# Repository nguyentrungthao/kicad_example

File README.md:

# Kiến thức thiết kế sơ đồ nguyên lý

- **Kiến thức cơ bản về điện tử**: [Playlist YouTube](https://www.youtube.com/playlist?list=PLGs3LoDo-2kOWhcLkcdEZovVq_vuPsPHr)
- **Kiến thức về các chuẩn giao tiếp của MCU**: I2C, SPI, UART
- **Kiến thức về nguồn**:
  - **Mạch lọc EMI**: [Video YouTube](https://www.youtube.com/watch?v=QAZo9xbiflQ&t=97s)
  - **Nguồn (Switching Power Supply)**: [Video YouTube](https://www.youtube.com/watch?v=2N_T7VFymFg)
  - **Nguồn xung Buck (Buck Converter)**: [Video YouTube](https://www.youtube.com/watch?v=W6NOV6b8kxs)

---

# KICAD

## Setup phần mềm cài plugin JLC và IBOM

### IBOM:
- [GitHub IBOM Plugin](https://github.com/openscopeproject/InteractiveHtmlBom)
- 

### JLCPCB:
- [GitHub JLCPCB Plugin](https://github.com/Bouni/kicad-jlcpcb-tools)
- **Link điền ở mục 4**: '''https://raw.githubusercontent.com/Bouni/bouni-kicad-repository/main/repository.json'''
- 

---

## Thiết kế phần cứng 
- $${\color{red} NHỚ ĐỌC TÀI LIỆU CỦA LINH KIỆN TRƯỚC KHI VẼ}$$

### Hướng dẫn thêm thư viện IoTVision vào KICAD

#### Thư viện có sẵn 
1. **Vào KICAD**.
2. **Chọn Preferences → Configure Paths**.
3. **Thêm đường dẫn thư viện**:
    - **3D**: Thêm alias như **IOTVISION_3D** và trỏ đường dẫn đến thư mục 3D step.
    - **Symbols**: Thêm alias như **IOTVISION_SYMBOL_DIR** và trỏ đường dẫn đến thư mục symbols.
    - **Footprints**: Thêm alias như **IOTVISION_FOOTPRINT_DIR** và trỏ đường dẫn đến thư mục footprints.
4. Nhấn **OK**.
5. **Quản lý thư viện**:
    - **Preferences → Manage Symbol Libraries → Global Libraries**.
    - Thêm **IVS_SYMBOLS** và đường dẫn thư viện **Symbols.kicad_sym**.
6. **Quản lý Footprint Libraries**:
    - Thêm **IVS_FOOTPRINTS** và đường dẫn **IVSFootprint.pretty**.

> **Lưu ý**: Nếu mở **PCB Editor** hoặc **Footprint Editor**, bạn sẽ không thấy **Manage Symbol Libraries**. 

#### Tải 3D và Footprint

- **Tìm footprint** <tên linh kiện> + <footprint> hoặc <tên linh kiện> + <digikey>
- **Tìm 3D** <tên linh kiện> + <3D> hoặc <Tên linh kiện> + <grabcad>

##### **Tải 3D**:
- [GrabCAD](https://grabcad.com/)
- [3D Content Central](https://www.3dcontentcentral.com/)

##### **Tải Footprint**:
- [SnapEDA](https://www.snapeda.com/)
- [Ultra Librarian](https://www.ultralibrarian.com/)
- [Digi-Key Footprint for Qualcomm RF Front End (RFFE) Filters](https://www.digikey.co.uk/en/products/detail/qualcomm-rf-front-end-rffe-filters/B39871B3725U410/3492646)

- **Video add thư viện**: [Hướng dẫn cài thư viện](https://youtu.be/sz3mICmpLzM)
- **video tìm add thư viện ngoài** [Tải thư viện ngoài - phút 12](https://www.youtube.com/watch?v=1mLzU-ezbA4&list=PLl72apUE_izgVsnWJDfx34R6ak8Qz5oGz&index=2&t=711s)
- **Thư viện cũ của LAB**: [IoTVision](https://github.com/IoTVision/HardwareLibrary)
- **Thư viện riêng của Tác giả** [KicadLIB](https://github.com/nguyentrungthao/KicadLibrary)
---
#### Schematic

1. **Lấy linh kiện**.
2. **Định nghĩa Bus I2C, SPI, Bus số (Demo vẽ insert)**.
3. **Sử dụng Netclass** (định nghĩa class, màu mè cho class).
4. **Thêm hình ảnh** vào Schematic.
5. **Thêm Footprint** cho linh kiện.
6. **Thêm giá trị linh kiện**.
7. **Vẽ Schematic**:
   - Đối với những bạn mới, nên thêm **Solder Jumper** để hạn chế cháy linh kiện.
8. **Thêm mã BOM** cho JLC, Thế Giới IC, IC Đầy Rối.
9. **Xuất BOM**.
10. **Xuất PDF**.

### Các bước khác:
- **Sửa và cập nhật symbol**.
- **Exclude linh kiện khỏi BOM**.
- **Xuất symbol vào thư viện riêng**.

---

#### PCB Design

1. **Thêm thư viện** vào PCB.
2. **Cấu hình board setup**:
   - Thêm/xóa các lớp (4 lớp, 6 lớp).
   - Cấu hình chữ, **Designed Rules**.
   - Cấu hình kích thước track, via, các netclass.
3. **Vẽ viền board** (đúng mm hoặc nhập file DXF).
4. **Vẽ kích thước board**, kích thước vị trí lỗ ốc.
5. **Tạo grid** tùy chỉnh.
6. **Cắt board tạo khoảng trống cách ly**.
7. **Update SCH sang PCB**.
8. **Sửa footprint trực tiếp**.
9. **Layout linh kiện**:
   - Xếp theo chụp các linh kiện, dùng các lệnh sắp xếp linh kiện.
   - Đặt connecter theo vỏ hộp từ đó đặt các linh kiện còn lại.
   - Chia vùng điện áp, vùng phủ đồng và giải thích các lựa chọn phủ đồng: thermal => sold, zone priority.
   - Dùng clearance và giải thích.
   - Rọc lớp đồng để phủ chì.
   - Sắp xếp tinh các linh kiện theo sơ đồ nguyên lý.
   - Đi dây:
     - Đi dây vi sai.
     - Hướng dẫn matching length.
     - Tính trở kháng đường dây.
     - Thêm các via GND.
     - Thêm teardrop.
10. **Xếp chữ ghi, chữ nổi đậm**, edit font chữ nhanh thêm thông tin, logo.
11. **Chạy DRC kiểm lỗi**.
12. **Xuất STEP**.
13. **Xuất PDF**.
14. **Xuất GERBER**.
15. **Xuất CPL**.
16. **Update file lên JLC để review**.

---

### Một số lỗi

- Viền board không nhận => chạy DRC sửa vị trí đỏ.

---
### Danh sách phát video kicad [Kicad play list](https://www.youtube.com/playlist?list=PLl72apUE_izgVsnWJDfx34R6ak8Qz5oGz) 

## HÀN MẠCH

- Học hàn, khò với thiết hàn cuộn và kem chì.
- Học cách tháo connector.

---

## DO NGUỘI

- Đo thông mạch nguồn, các đường tín hiệu trước khi cắm điện.

---

## LẬP TRÌNH TEST MẠCH

- Test nạp code ESP32 => nếu không tự động nạp được, xem lại mạch nút nhấn BOOT và RESET của ESP32.
- Viết code test từng module trên PCB.

## Project Mẫu 
- **STM32F103** [Đồ án môn học - PID Lò nhiệt](https://github.com/nguyentrungthao/AcademicProject2_v2)
- **projet mẫu** [mạch mẫu theo link học tập của Thầy TS.Nguyễn Văn Thái](https://github.com/nguyentrungthao/kicad_example/tree/main/train1)
- **Link bài học của Thầy Nguyễn Văn Thái** [Bài Giảng](https://docs.google.com/document/d/1S12LlzbIVofPXDoD7pqb3iYUZ_utdi-w3tmKryJMrkk/edit?tab=t.0)

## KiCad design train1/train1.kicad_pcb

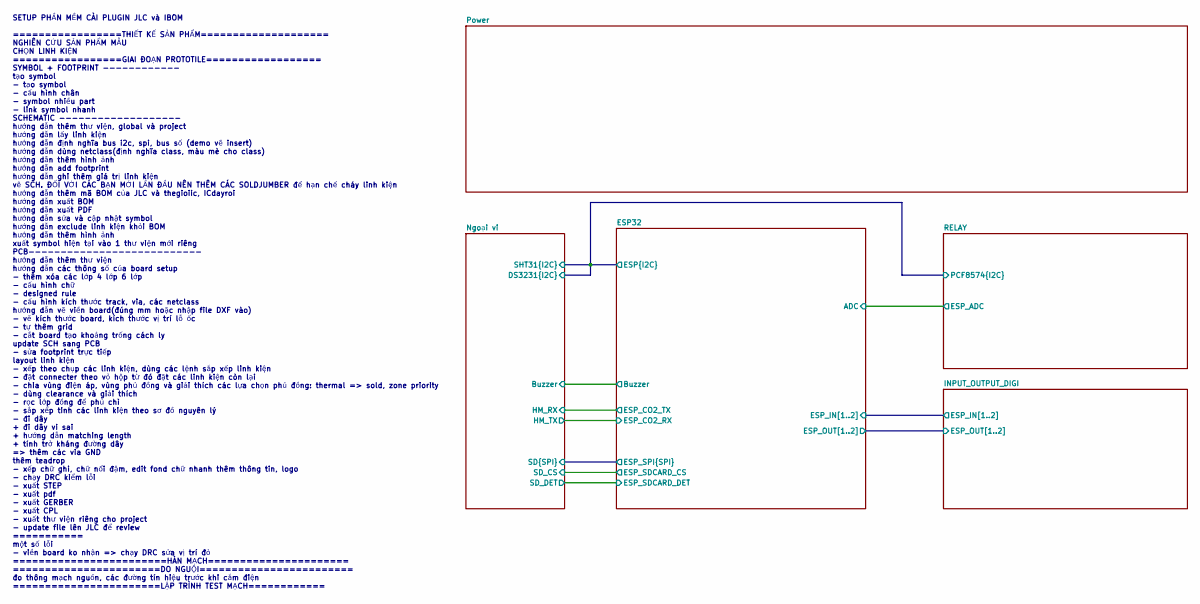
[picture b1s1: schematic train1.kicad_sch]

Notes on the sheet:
SETUP PHẦN MỀM CÀI PLUGIN JLC và IBOM =================THIẾT KẾ SẢN PHẨM==================== NGHIÊN CỨU SẢN PHẨM MẪU CHỌN LINH KIỆN =================GIAI ĐOẠN PROTOTILE================== SYMBOL + FOOTPRINT ------------ tạo symbol - tạo symbol - cấu hình chân - symbol nhiều part - link symbol nhanh 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

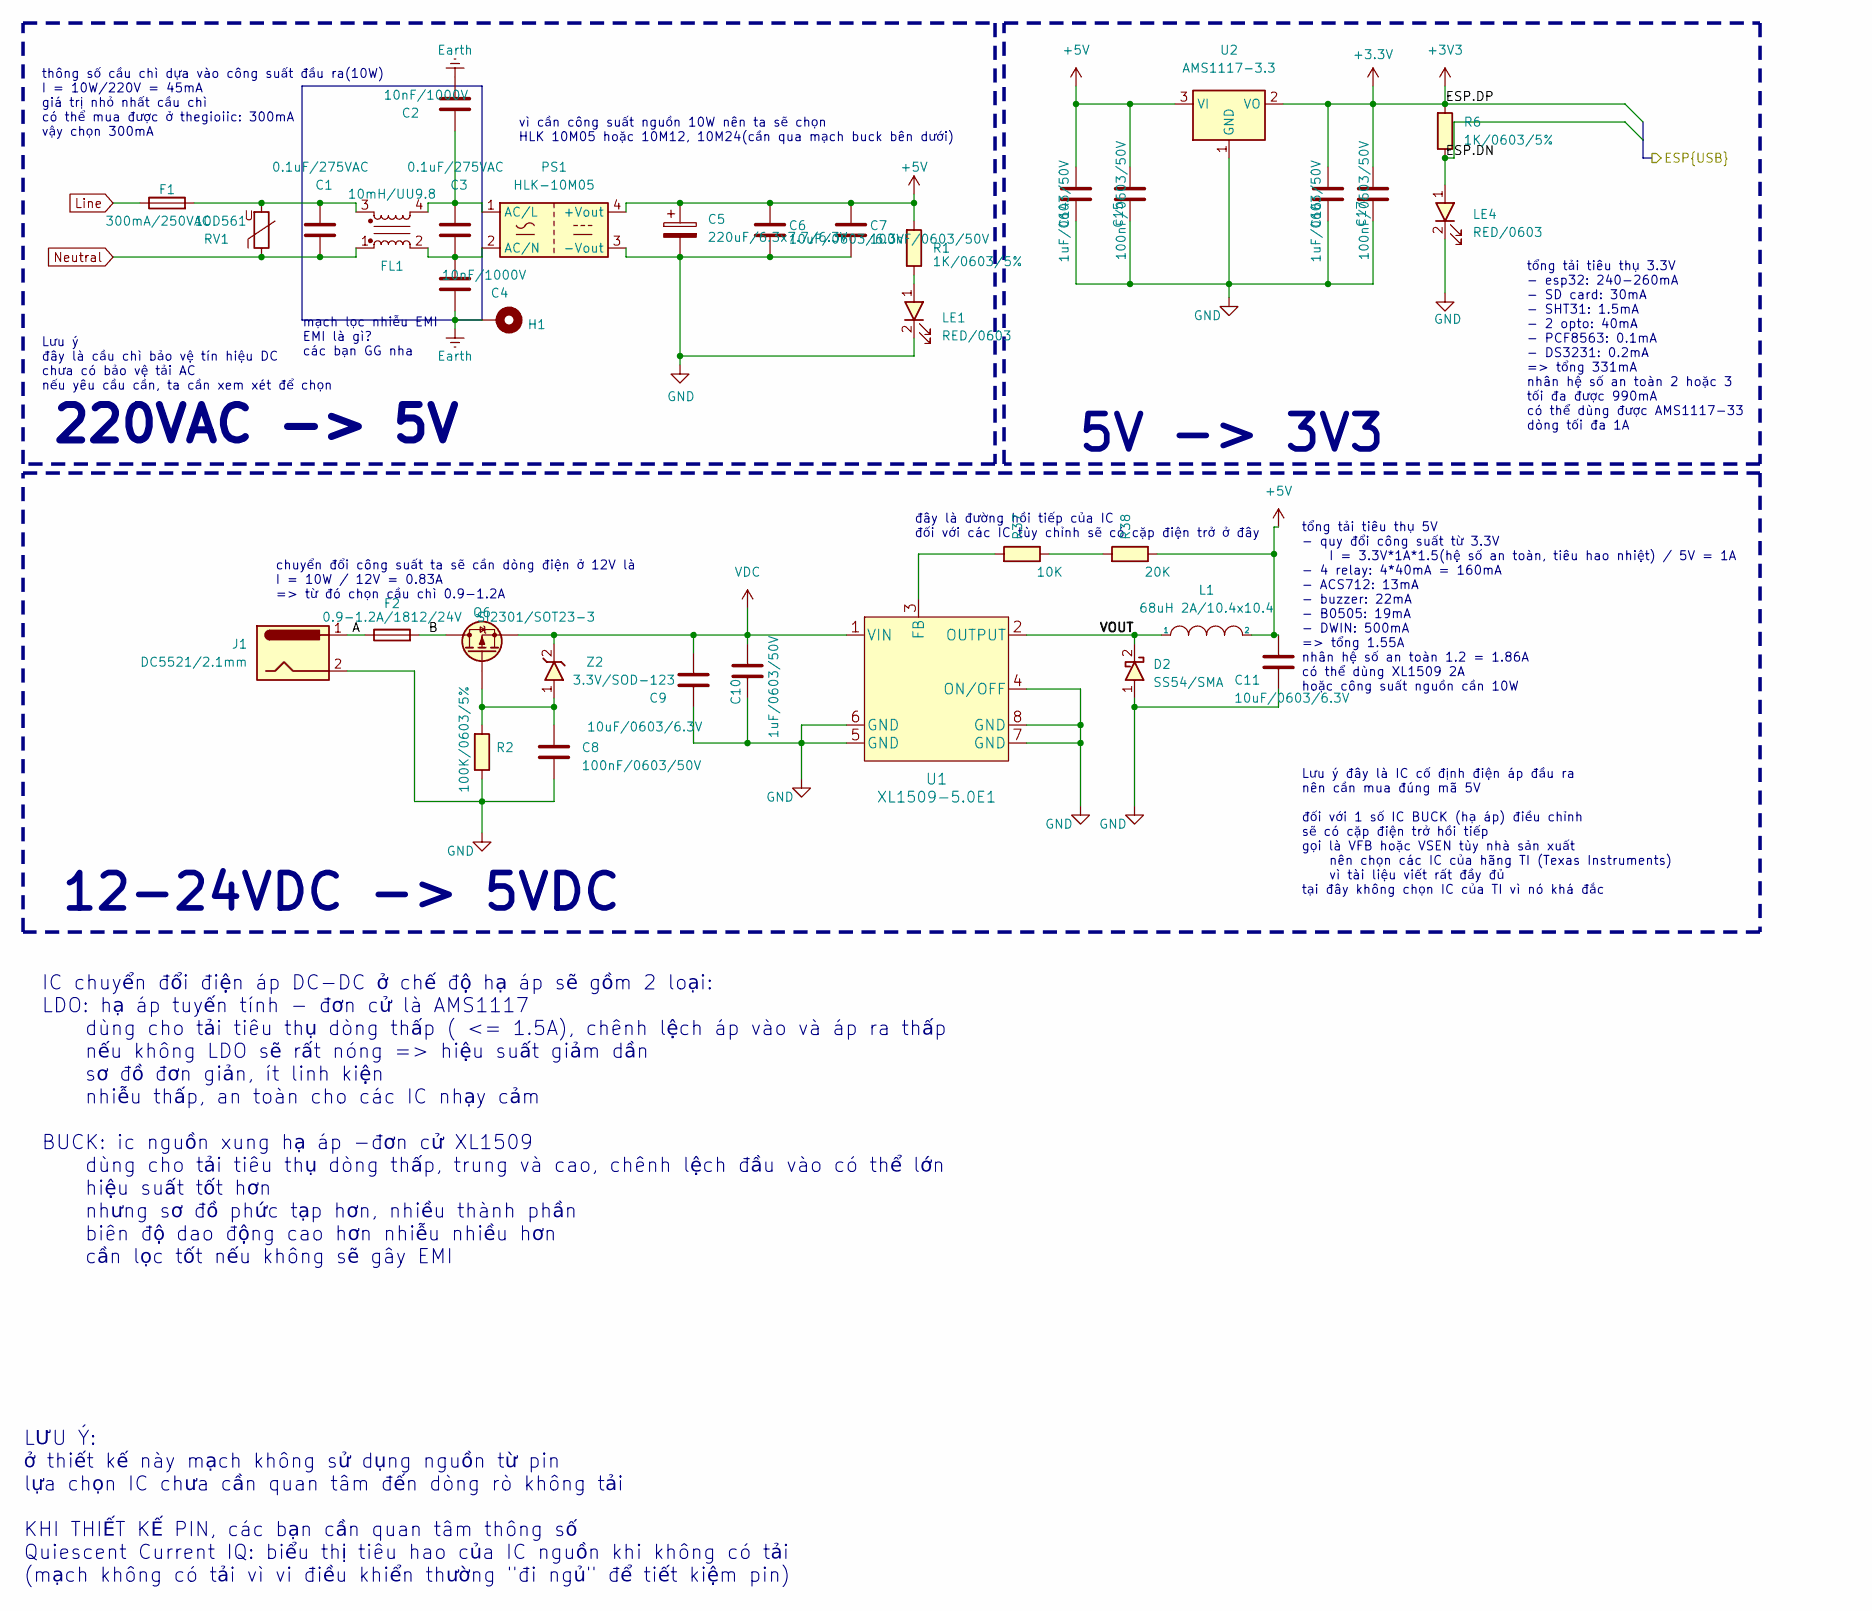
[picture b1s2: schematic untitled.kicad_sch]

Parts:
C1, C3: 0.1uF/275VAC; C_Rect_L16.5mm_W5.0mm_P15.00mm_MKT
C2, C4: 10nF/1000V; C_Rect_L7.0mm_W2.0mm_P5.00mm
C5: 220uF/6.3x7.7/6.3V; CP_Elec_6.3x7.7
C6, C9, C11: 10uF/0603/6.3V; C_0603
C7, C8, C15, C17: 100nF/0603/50V; C_0603
C10, C14, C16: 1uF/0603/50V; C_0603
D2: SS54/SMA; D_SMA
F1: 300mA/250VAC; RV_Disc_D12mm_W3.9mm_P7.5mm
F2: 0.9-1.2A/1812/24V; Fuse_1812_4532Metric
FL1: 10mH/UU9.8; ACFilterChokeUU9.8
H1: MountingHole_Pad; MountingHole_3.2mm_M3_Pad_Via
J1: DC5521/2.1mm; BarrelJack_Wuerth_6941xx301002
L1: 68uH 2A/10.4x10.4; L_10.4x10.4_H4.8
LE1, LE4: RED/0603; LED_0603
PS1: HLK-10M05; ACDC_HLK10M05
Q6: SI2301/SOT23-3; SOT23-3
R1, R6: 1K/0603/5%; C_0603
R2: 100K/0603/5%; C_0603
R37: 10K; C_0603
R38: 20K; C_0603
RV1: 10D561; RV_Disc_D12mm_W5.8mm_P7.5mm
U1: XL1509-5.0E1; SOIC-8_3.9x4.9mm_P1.27mm
U2: AMS1117-3.3; SOT-223-3_TabPin2
Z2: 3.3V/SOD-123; D_SOD-123

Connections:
+3.3V: C16.2, C17.2, R6.1, U2.2 (VO); also elsewhere on the board
+5V: C5.1, C6.1, C7.1, C11.1, C14.2, C15.2, L1.2, PS1.4 (+Vout), R1.1, R38.2, U2.3 (VI); also elsewhere on the board
/Power/A: F2.1, J1.1
/Power/B: F2.2, Q6.3 (D)
/Power/ESP.DN: LE4.1, R6.2
/Power/VOUT: D2.2, L1.1, U1.2 (OUTPUT)
Earth: C2.2, C4.1, H1.1
GND: C5.2, C6.2, C7.2, C8.2, C9.2, C10.1, C11.2, C14.1, C15.1, C16.1, C17.1, D2.1, J1.2, LE1.2, LE4.2, PS1.3 (-Vout), R2.2, U1.4 (ON/OFF), U1.5 (GND), U1.6 (GND), U1.7 (GND), U1.8 (GND), U2.1 (GND); also elsewhere on the board
Line: F1.1; also elsewhere on the board
unnamed: C1.2, F1.2, FL1.3, RV1.2
unnamed: LE1.1, R1.2
unnamed: C2.1, C3.2, FL1.4, PS1.1 (AC/L)
unnamed: C3.1, C4.2, FL1.2, PS1.2 (AC/N)
unnamed: C8.1, Q6.1 (G), R2.1, Z2.1
unnamed: R37.2, R38.1
unnamed: R37.1, U1.3 (FB)
Neutral: C1.1, FL1.1, RV1.1; also elsewhere on the board
VDC: C9.1, C10.2, Q6.2 (S), U1.1 (VIN), Z2.2

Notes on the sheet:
5V -> 3V3
Lưu ý đây là IC cố định điện áp đầu ra nên cần mua đúng mã 5V đối với 1 số IC BUCK (hạ áp) điều chỉnh sẽ có cặp điện trở hồi tiếp gọi là VFB hoặc VSEN tùy nhà sản xuất nên chọn các IC của hãng TI (Texas Instruments) vì tài liệu viết rất đầy đủ tại đây không chọn IC của TI vì nó khá đắc
đây là đường hồi tiếp của IC đối với các IC tùy chỉnh sẽ có cặp điện trở ở đây
LƯU Ý: ở thiết kế này mạch không sử dụng nguồn từ pin lựa chọn IC chưa cần quan tâm đến dòng rò không tải KHI THIẾT KẾ PIN, các bạn cần quan tâm thông số Quiescent Current IQ: biểu thị tiêu hao của IC nguồn khi không có tải (mạch không có tải vì vi điều khiển thường "đi ngủ" để tiết kiệm pin)
chuyển đổi công suất ta sẽ cần dòng điện ở 12V là I = 10W / 12V = 0.83A => từ đó chọn cầu chì 0.9-1.2A
mạch lọc nhiễu EMI EMI là gì? các bạn GG nha
Lưu ý đây là cầu chì bảo vệ tín hiệu DC chưa có bảo vệ tải AC nếu yêu cầu cần, ta cần xem xét để chọn
IC chuyển đổi điện áp DC-DC ở chế độ hạ áp sẽ gồm 2 loại: LDO: hạ áp tuyến tính - đơn cử là AMS1117 dùng cho tải tiêu thụ dòng thấp ( <= 1.5A), chênh lệch áp vào và áp ra thấp nếu không LDO sẽ rất nóng => hiệu suất giảm dần sơ đồ đơn giản, ít linh kiện nhiễu thấp, an toàn cho các IC nhạy cảm BUCK: 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
thông số cầu chì dựa vào công suất đầu ra(10W) I = 10W/220V = 45mA giá trị nhỏ nhất cầu chì có thể mua được ở thegioiic: 300mA vậy chọn 300mA
vì cần công suất nguồn 10W nên ta sẽ chọn HLK 10M05 hoặc 10M12, 10M24(cần qua mạch buck bên dưới)
220VAC -> 5V
12-24VDC -> 5VDC
tổng tải tiêu thụ 3.3V - esp32: 240-260mA - SD card: 30mA - SHT31: 1.5mA - 2 opto: 40mA - PCF8563: 0.1mA - DS3231: 0.2mA => tổng 331mA nhân hệ số an toàn 2 hoặc 3 tối đa được 990mA có thể dùng được AMS1117-33 dòng tối đa 1A
tổng tải tiêu thụ 5V - quy đổi công suất từ 3.3V I = 3.3V*1A*1.5(hệ số an toàn, tiêu hao nhiệt) / 5V = 1A - 4 relay: 4*40mA = 160mA - ACS712: 13mA - buzzer: 22mA - B0505: 19mA - DWIN: 500mA => tổng 1.55A nhân hệ số an toàn 1.2 = 1.86A có thể dùng XL1509 2A hoặc công suất nguồn cần 10W

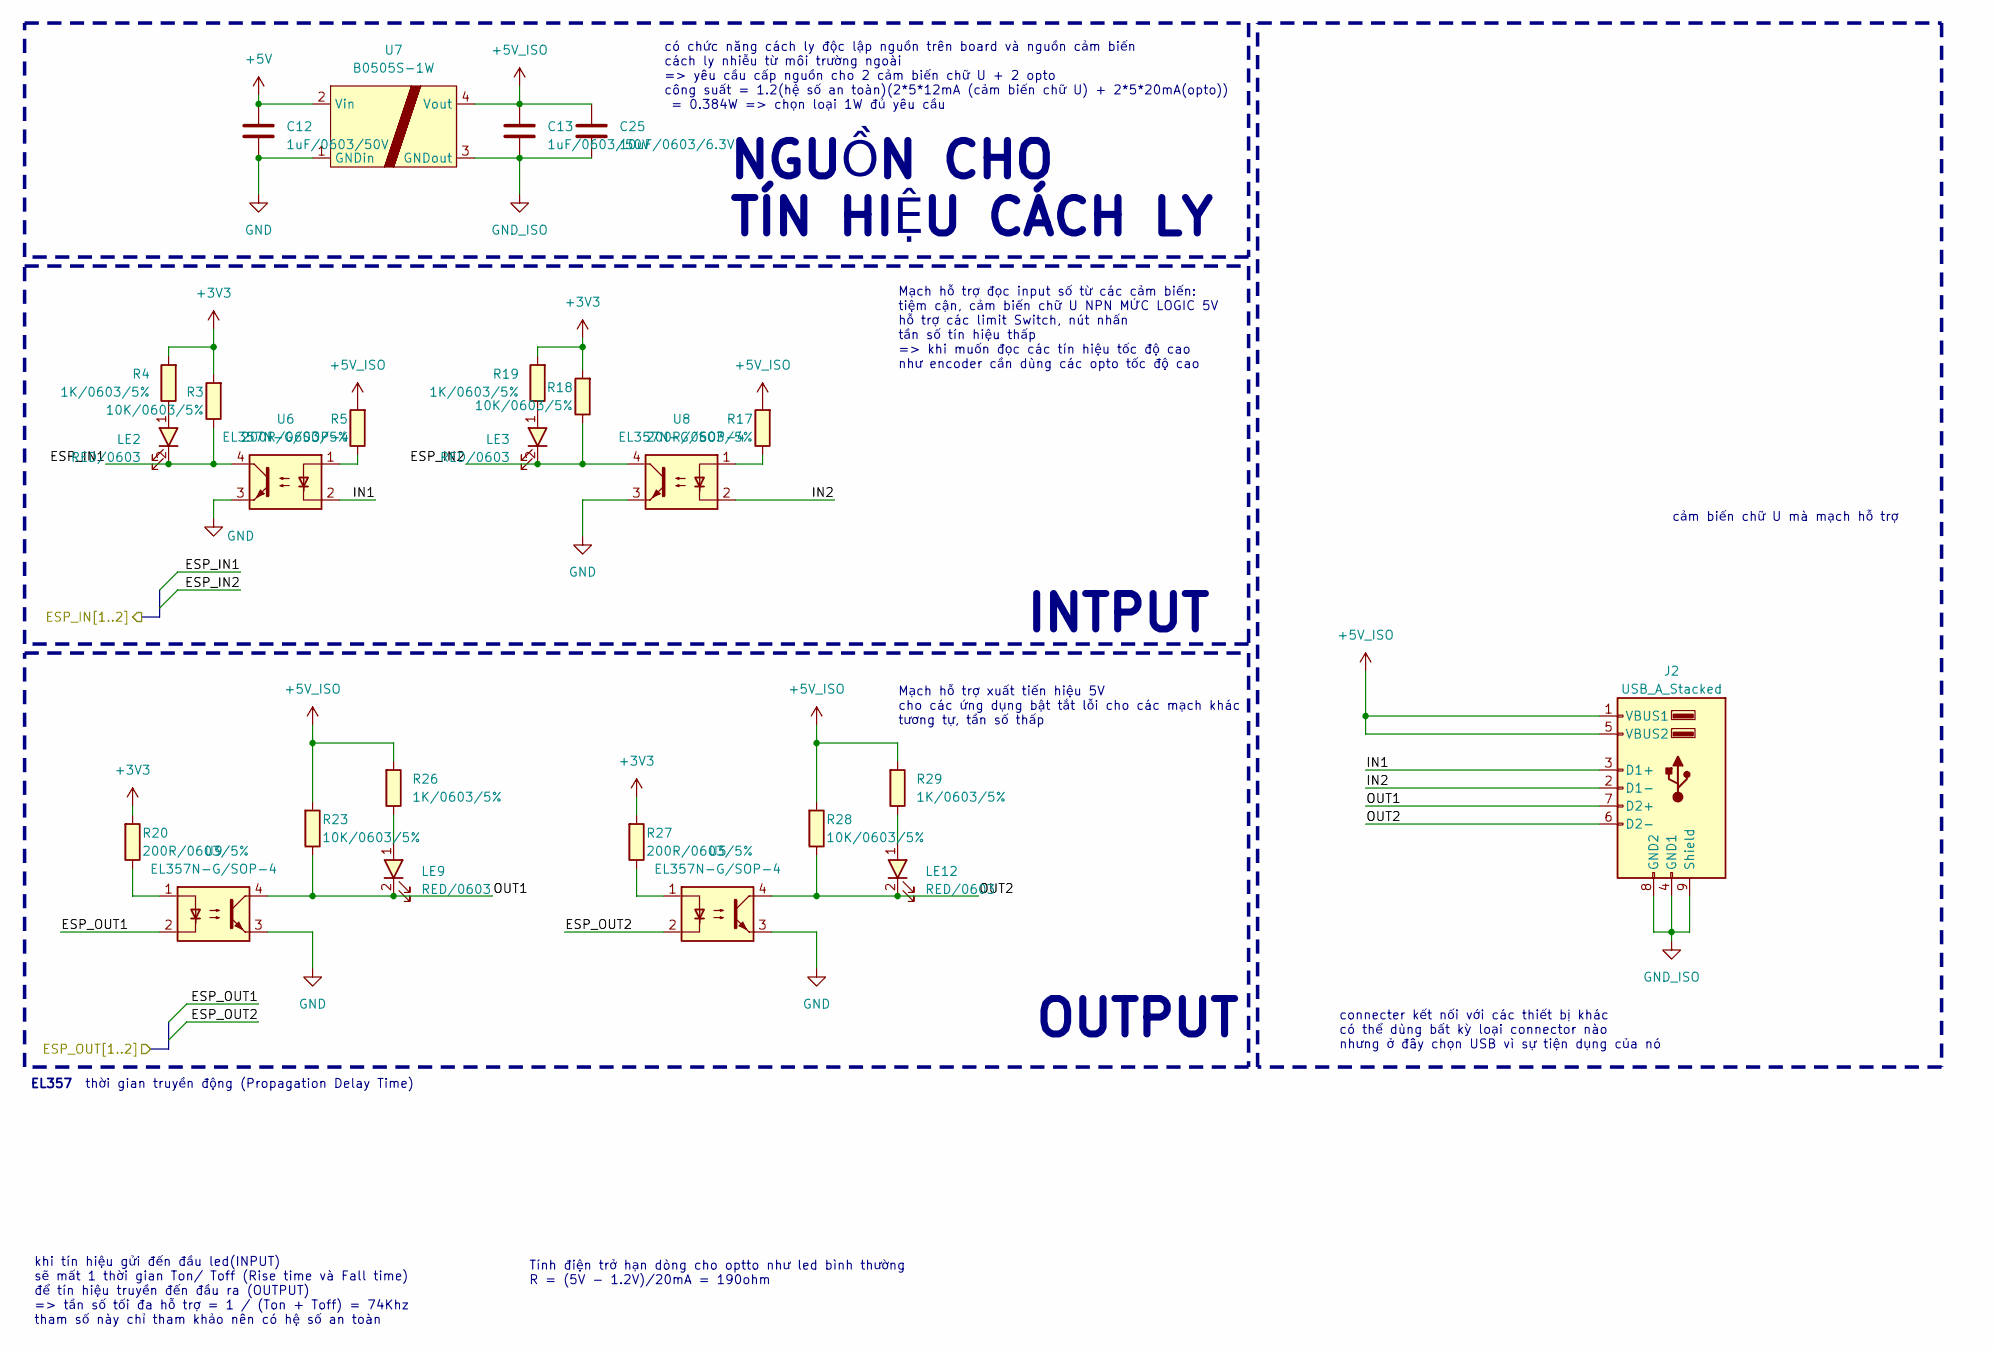
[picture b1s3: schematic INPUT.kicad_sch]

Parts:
C12, C13: 1uF/0603/50V; C_0603
C25: 10uF/0603/6.3V; C_0603
J2: USB_A_Stacked; USB_A_Wuerth_61400826021_Horizontal_Stacked
LE2, LE3, LE9, LE12: RED/0603; LED_0603
R3, R18, R23, R28: 10K/0603/5%; C_0603
R4, R19, R26, R29: 1K/0603/5%; C_0603
R5, R17, R20, R27: 200R/0603/5%; C_0603
U5, U6, U8, U9: EL357N-G/SOP-4; OPTO_EL357N-G
U7: B0505S-1W; B0505S

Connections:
+3.3V: R3.1, R4.1, R18.1, R19.1, R20.1, R27.1; also elsewhere on the board
+5V: C12.1, U7.2 (Vin); also elsewhere on the board
+5V_ISO: C13.1, C25.1, J2.1 (VBUS1), J2.5 (VBUS2), R5.1, R17.1, R23.1, R26.1, R28.1, R29.1, U7.4 (Vout)
/ESP32/ESP_IN1: LE2.2, R3.2, U6.4; also elsewhere on the board
/ESP32/ESP_IN2: LE3.2, R18.2, U8.4; also elsewhere on the board
/ESP32/ESP_OUT1: U9.2; also elsewhere on the board
/ESP32/ESP_OUT2: U5.2; also elsewhere on the board
/INPUT_OUTPUT_DIGI/IN1: J2.3 (D1+), U6.2
/INPUT_OUTPUT_DIGI/IN2: J2.2 (D1-), U8.2
/INPUT_OUTPUT_DIGI/OUT1: J2.7 (D2+), LE9.2, R23.2, U9.4
/INPUT_OUTPUT_DIGI/OUT2: J2.6 (D2-), LE12.2, R28.2, U5.4
GND: C12.2, U5.3, U6.3, U7.1 (GNDin), U8.3, U9.3; also elsewhere on the board
GND_ISO: C13.2, C25.2, J2.4 (GND1), J2.8 (GND2), J2.9 (Shield), U7.3 (GNDout)
unnamed: LE2.1, R4.2
unnamed: LE3.1, R19.2
unnamed: LE9.1, R26.2
unnamed: LE12.1, R29.2
unnamed: R5.2, U6.1
unnamed: R17.2, U8.1
unnamed: R20.2, U9.1
unnamed: R27.2, U5.1

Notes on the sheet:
cảm biến chữ U mà mạch hỗ trợ
OUTPUT
khi tín hiệu gửi đến đầu led(INPUT) sẽ mất 1 thời gian Ton/ Toff (Rise time và Fall time) để tín hiệu truyền đến đầu ra (OUTPUT) => tần số tối đa hỗ trợ = 1 / (Ton + Toff) = 74Khz tham số này chỉ tham khảo nên có hệ số an toàn
connecter kết nối với các thiết bị khác có thể dùng bất kỳ loại connector nào nhưng ở đây chọn USB vì sự tiện dụng của nó
Tính điện trở hạn dòng cho optto như led bình thường R = (5V - 1.2V)/20mA = 190ohm
Mạch hỗ trợ đọc input số từ các cảm biến: tiệm cận, cảm biến chữ U NPN MỨC LOGIC 5V hỗ trợ các limit Switch, nút nhấn tần số tín hiệu thấp => khi muốn đọc các tín hiệu tốc độ cao như encoder cần dùng các opto tốc độ cao
thời gian truyền động (Propagation Delay Time)
EL357
NGUỒN CHO TÍN HIỆU CÁCH LY
có chức năng cách ly độc lập nguồn trên board và nguồn cảm biến cách ly nhiễu từ môi trường ngoài => yêu cầu cấp nguồn cho 2 cảm biến chữ U + 2 opto công suất = 1.2(hệ số an toàn)(2*5*12mA (cảm biến chữ U) + 2*5*20mA(opto)) = 0.384W => chọn loại 1W đủ yêu cầu
INTPUT
Mạch hỗ trợ xuất tiến hiệu 5V cho các ứng dụng bật tắt lỗi cho các mạch khác tương tự, tần số thấp

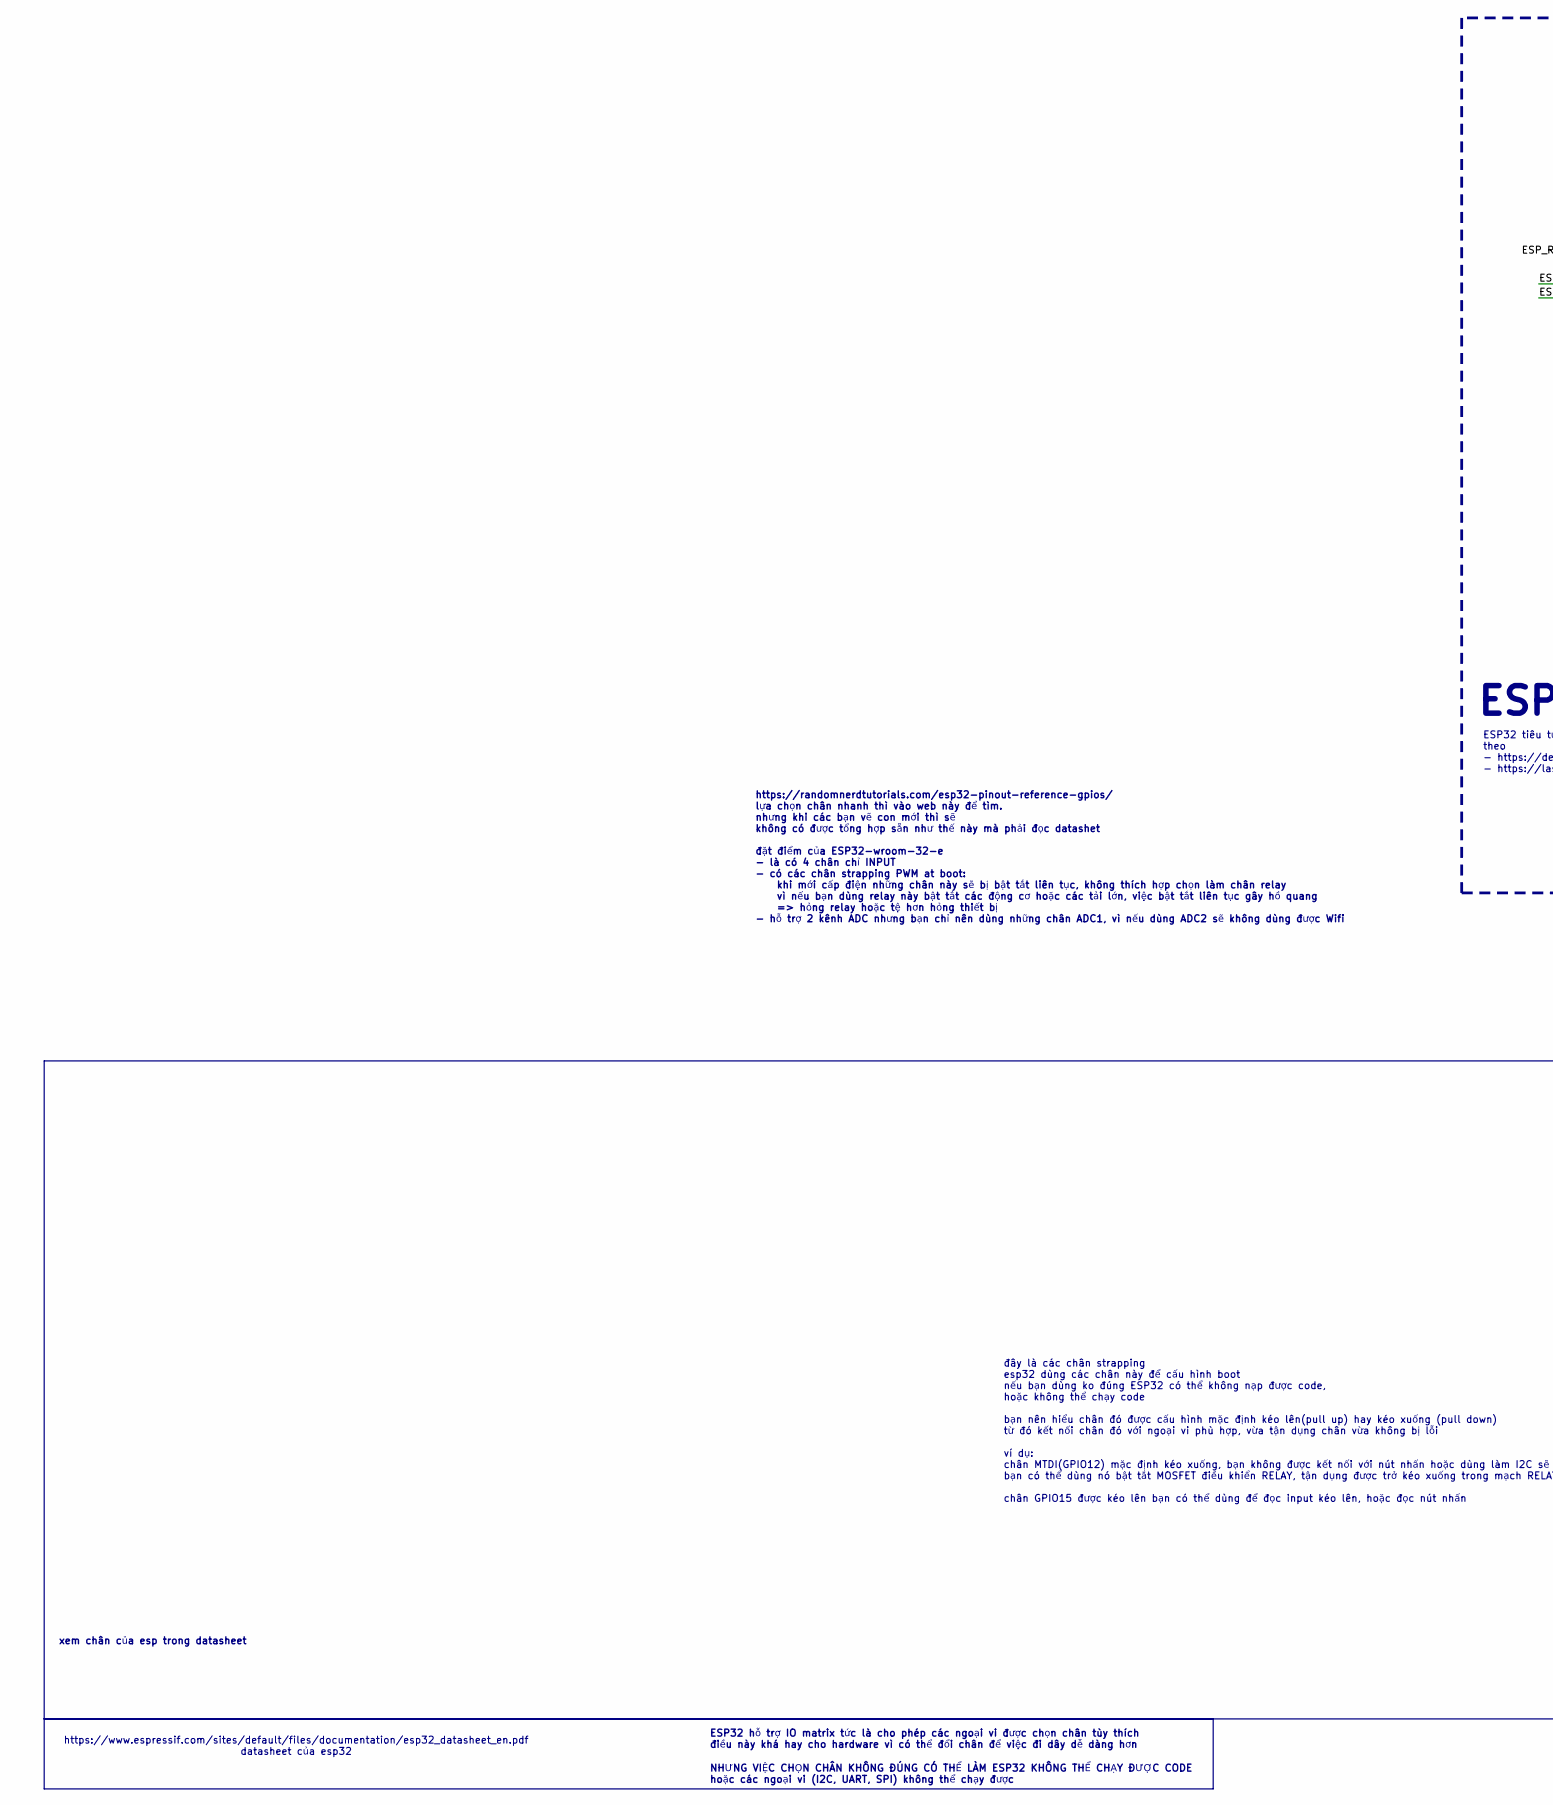
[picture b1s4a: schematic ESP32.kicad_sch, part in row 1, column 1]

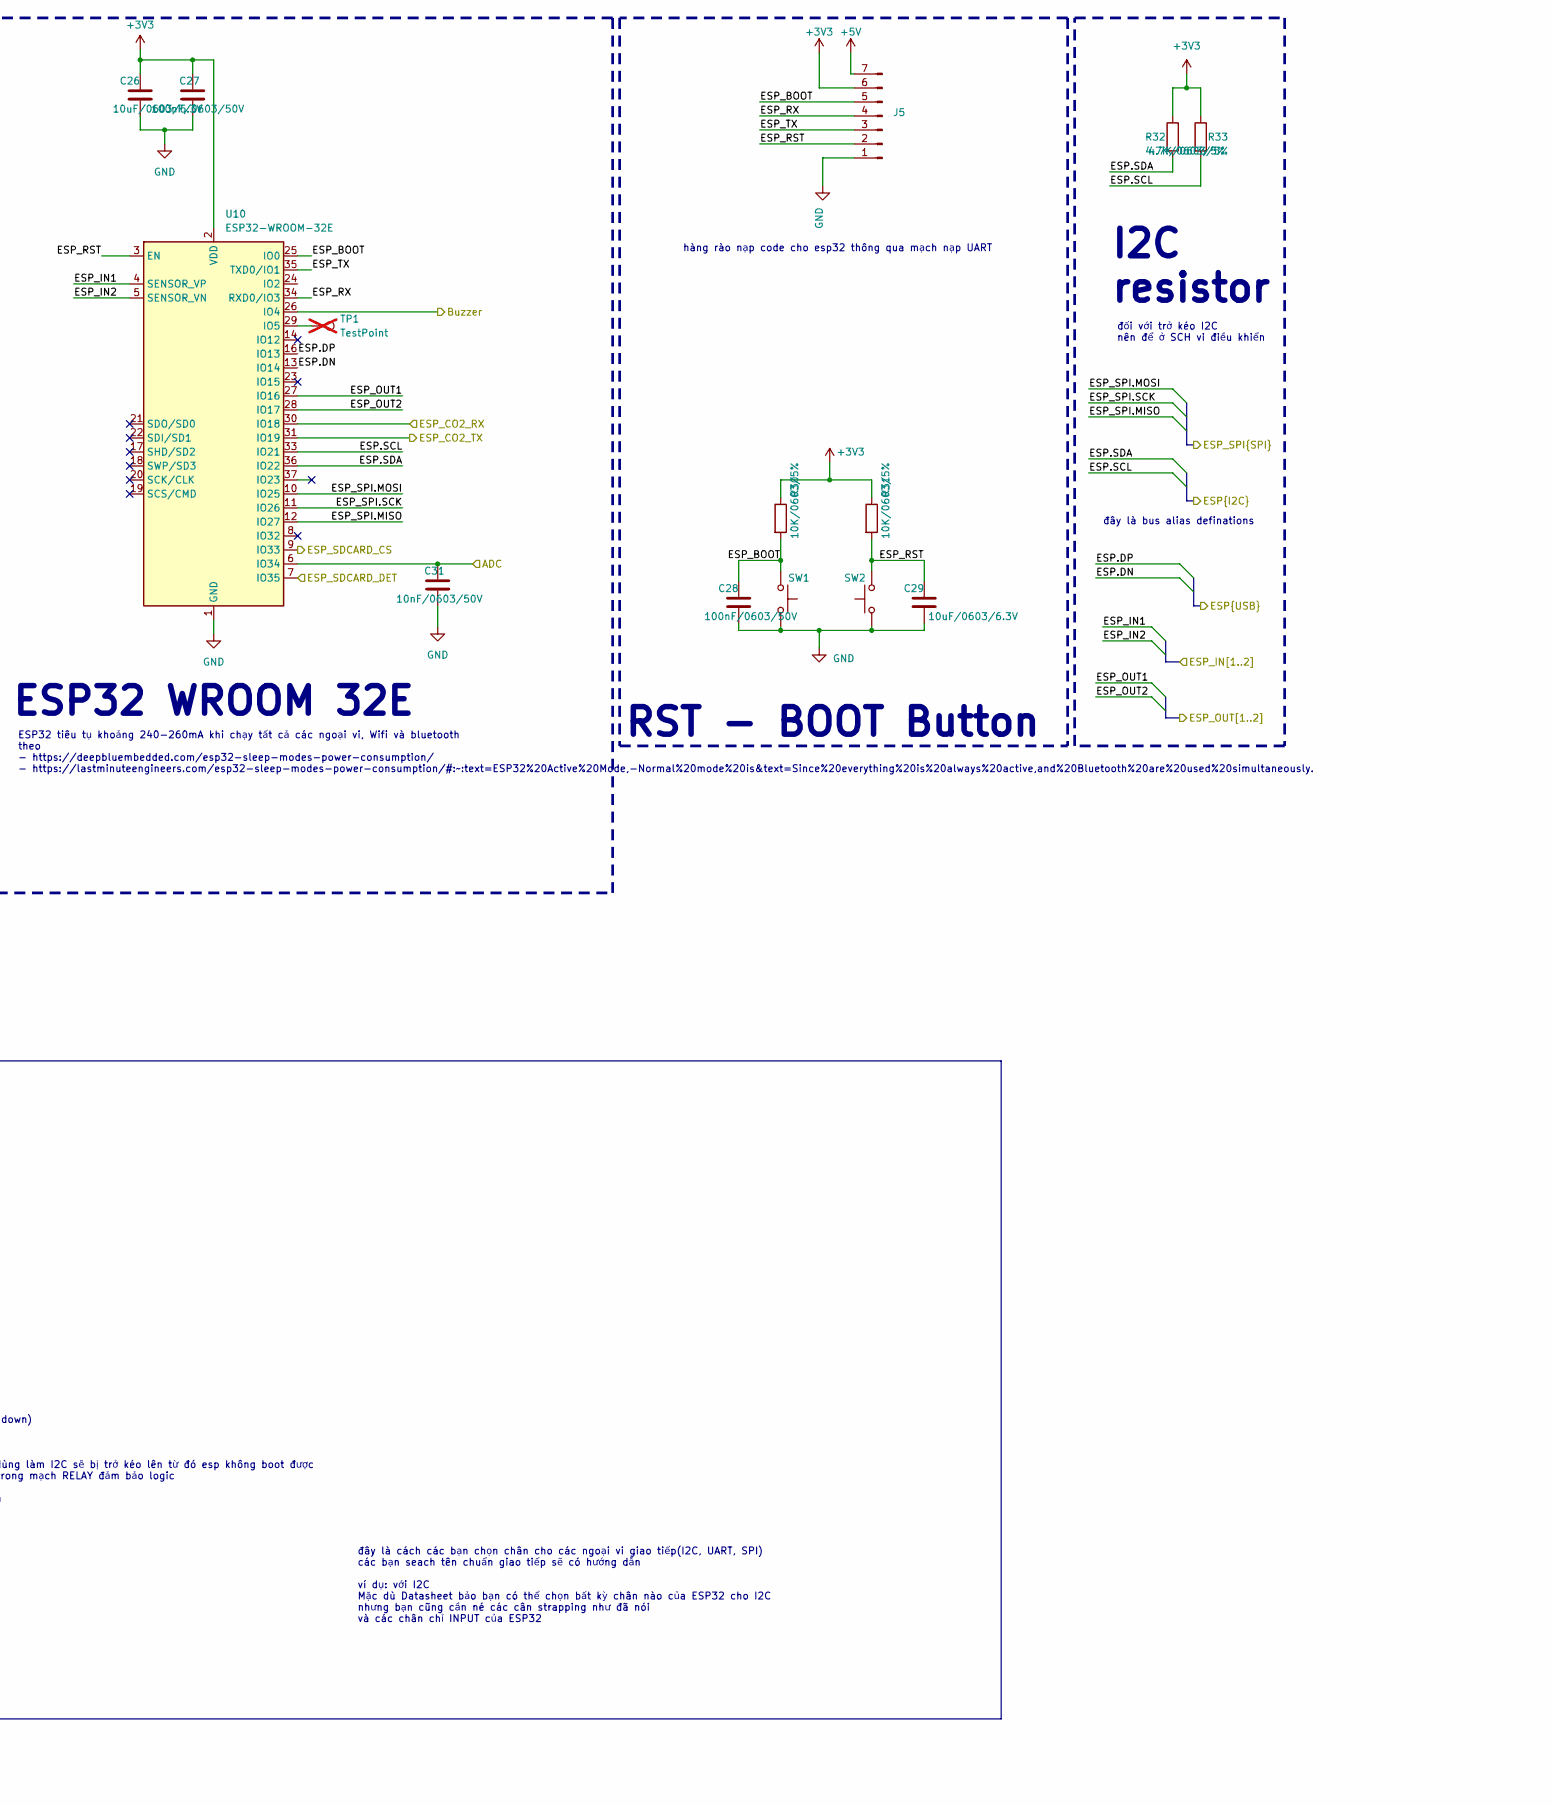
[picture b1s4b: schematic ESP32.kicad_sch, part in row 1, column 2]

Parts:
C26, C29: 10uF/0603/6.3V; C_0603; Part number LM7805CT
C27, C28: 100nF/0603/50V; C_0603
C31: 10nF/0603/50V; C_0603
J5: header-2.54mm-7p; PinHeader_1x07_P2.54mm_Vertical
R30, R31: 10K/0603/5%; C_0603
R32, R33: 4.7K/0603/5%; C_0603
SW1, SW2: tactileSW/4.2x3.3; SW_SPST_PTS810
TP1: TestPoint; TestPoint_Pad_D1.0mm; not fitted
U10: ESP32-WROOM-32E

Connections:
+3.3V: C26.1, C27.1, J5.6, R30.1, R31.1, R32.1, R33.1, U10.2 (VDD); also elsewhere on the board
+5V: J5.7; also elsewhere on the board
/ESP32/ADC: C31.1, U10.6 (IO34); also elsewhere on the board
/ESP32/ESP.DN: U10.13 (IO14)
/ESP32/ESP.DP: U10.16 (IO13)
/ESP32/ESP_BOOT: C28.1, J5.5, R30.2, SW1.1, U10.25 (IO0)
/ESP32/ESP_CO2_RX: U10.30 (IO18); also elsewhere on the board
/ESP32/ESP_CO2_TX: U10.31 (IO19); also elsewhere on the board
/ESP32/ESP_IN1: U10.4 (SENSOR_VP); also elsewhere on the board
/ESP32/ESP_IN2: U10.5 (SENSOR_VN); also elsewhere on the board
/ESP32/ESP_OUT1: U10.27 (IO16); also elsewhere on the board
/ESP32/ESP_OUT2: U10.28 (IO17); also elsewhere on the board
/ESP32/ESP_RST: C29.1, J5.2, R31.2, SW2.2, U10.3 (EN)
/ESP32/ESP_RX: J5.4, U10.34 (RXD0/IO3)
/ESP32/ESP_SDCARD_CS: U10.9 (IO33); also elsewhere on the board
/ESP32/ESP_SDCARD_DET: U10.7 (IO35); also elsewhere on the board
/ESP32/ESP_SPI.MISO: U10.12 (IO27); also elsewhere on the board
/ESP32/ESP_SPI.MOSI: U10.10 (IO25); also elsewhere on the board
/ESP32/ESP_SPI.SCK: U10.11 (IO26); also elsewhere on the board
/ESP32/ESP_TX: J5.3, U10.35 (TXD0/IO1)
Buzzer: U10.26 (IO4); also elsewhere on the board
GND: C26.2, C27.2, C28.2, C29.2, C31.2, J5.1, SW1.2, SW2.1, U10.1 (GND), U10.15 (GND), U10.38 (GND), U10.39 (GND); also elsewhere on the board
unnamed: TP1.1, U10.29 (IO5)

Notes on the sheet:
ESP32 WROOM 32E
hàng rào nạp code cho esp32 thông qua mạch nạp UART
https://randomnerdtutorials.com/esp32-pinout-reference-gpios/ lựa chọn chân nhanh thì vào web này để tìm. nhưng khi các bạn vẽ con mới thì sẽ không có được tổng hợp sẵn như thế này mà phải đọc datashet đặt điểm của ESP32-wroom-32-e - là có 4 chân chỉ INPUT - có các chân strapping PWM at boot: khi m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
xem chân của esp trong datasheet
RST - BOOT Button
NHƯNG VIỆC CHỌN CHÂN KHÔNG ĐÚNG CÓ THỂ LÀM ESP32 KHÔNG THỂ CHẠY ĐƯỢC CODE hoặc các ngoại vi (I2C, UART, SPI) không thể chạy được
đối với trở kéo I2C nên để ở SCH vi điều khiển
đây là các chân strapping esp32 dùng các chân này để cấu hình boot nếu bạn dùng ko đúng ESP32 có thể không nạp được code, hoặc không thể chạy code bạn nên hiểu chân đó được cấu hình mặc định kéo lên(pull up) hay kéo xuống (pull down) từ đó kết nối chân đó với ngoại vi phù hợp, vừa tận dụng chân vừa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
đây là bus alias definations
https://www.espressif.com/sites/default/files/documentation/esp32_datasheet_en.pdf datasheet của esp32
ESP32 hỗ trợ IO matrix tức là cho phép các ngoại vi được chọn chân tùy thích điều này khá hay cho hardware vì có thể đổi chân để việc đi dây dễ dàng hơn
I2C resistor
đây là cách các bạn chọn chân cho các ngoại vi giao tiếp(I2C, UART, SPI) các bạn seach tên chuẩn giao tiếp sẽ có hướng dẫn ví dụ: với I2C Mặc dù Datasheet bảo bạn có thể chọn bất kỳ chân nào của ESP32 cho I2C nhưng bạn cũng cần né các cân strapping như đã nói và các chân chỉ INPUT của ESP32
ESP32 tiêu tụ khoảng 240-260mA khi chạy tất cả các ngoại vi, Wifi và bluetooth theo - https://deepbluembedded.com/esp32-sleep-modes-power-consumption/ - https://lastminuteengineers.com/esp32-sleep-modes-power-consumption/#:~:text=ESP32%20Active%20Mode,-Normal%20mode%20is&text=Since%20everything%20i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

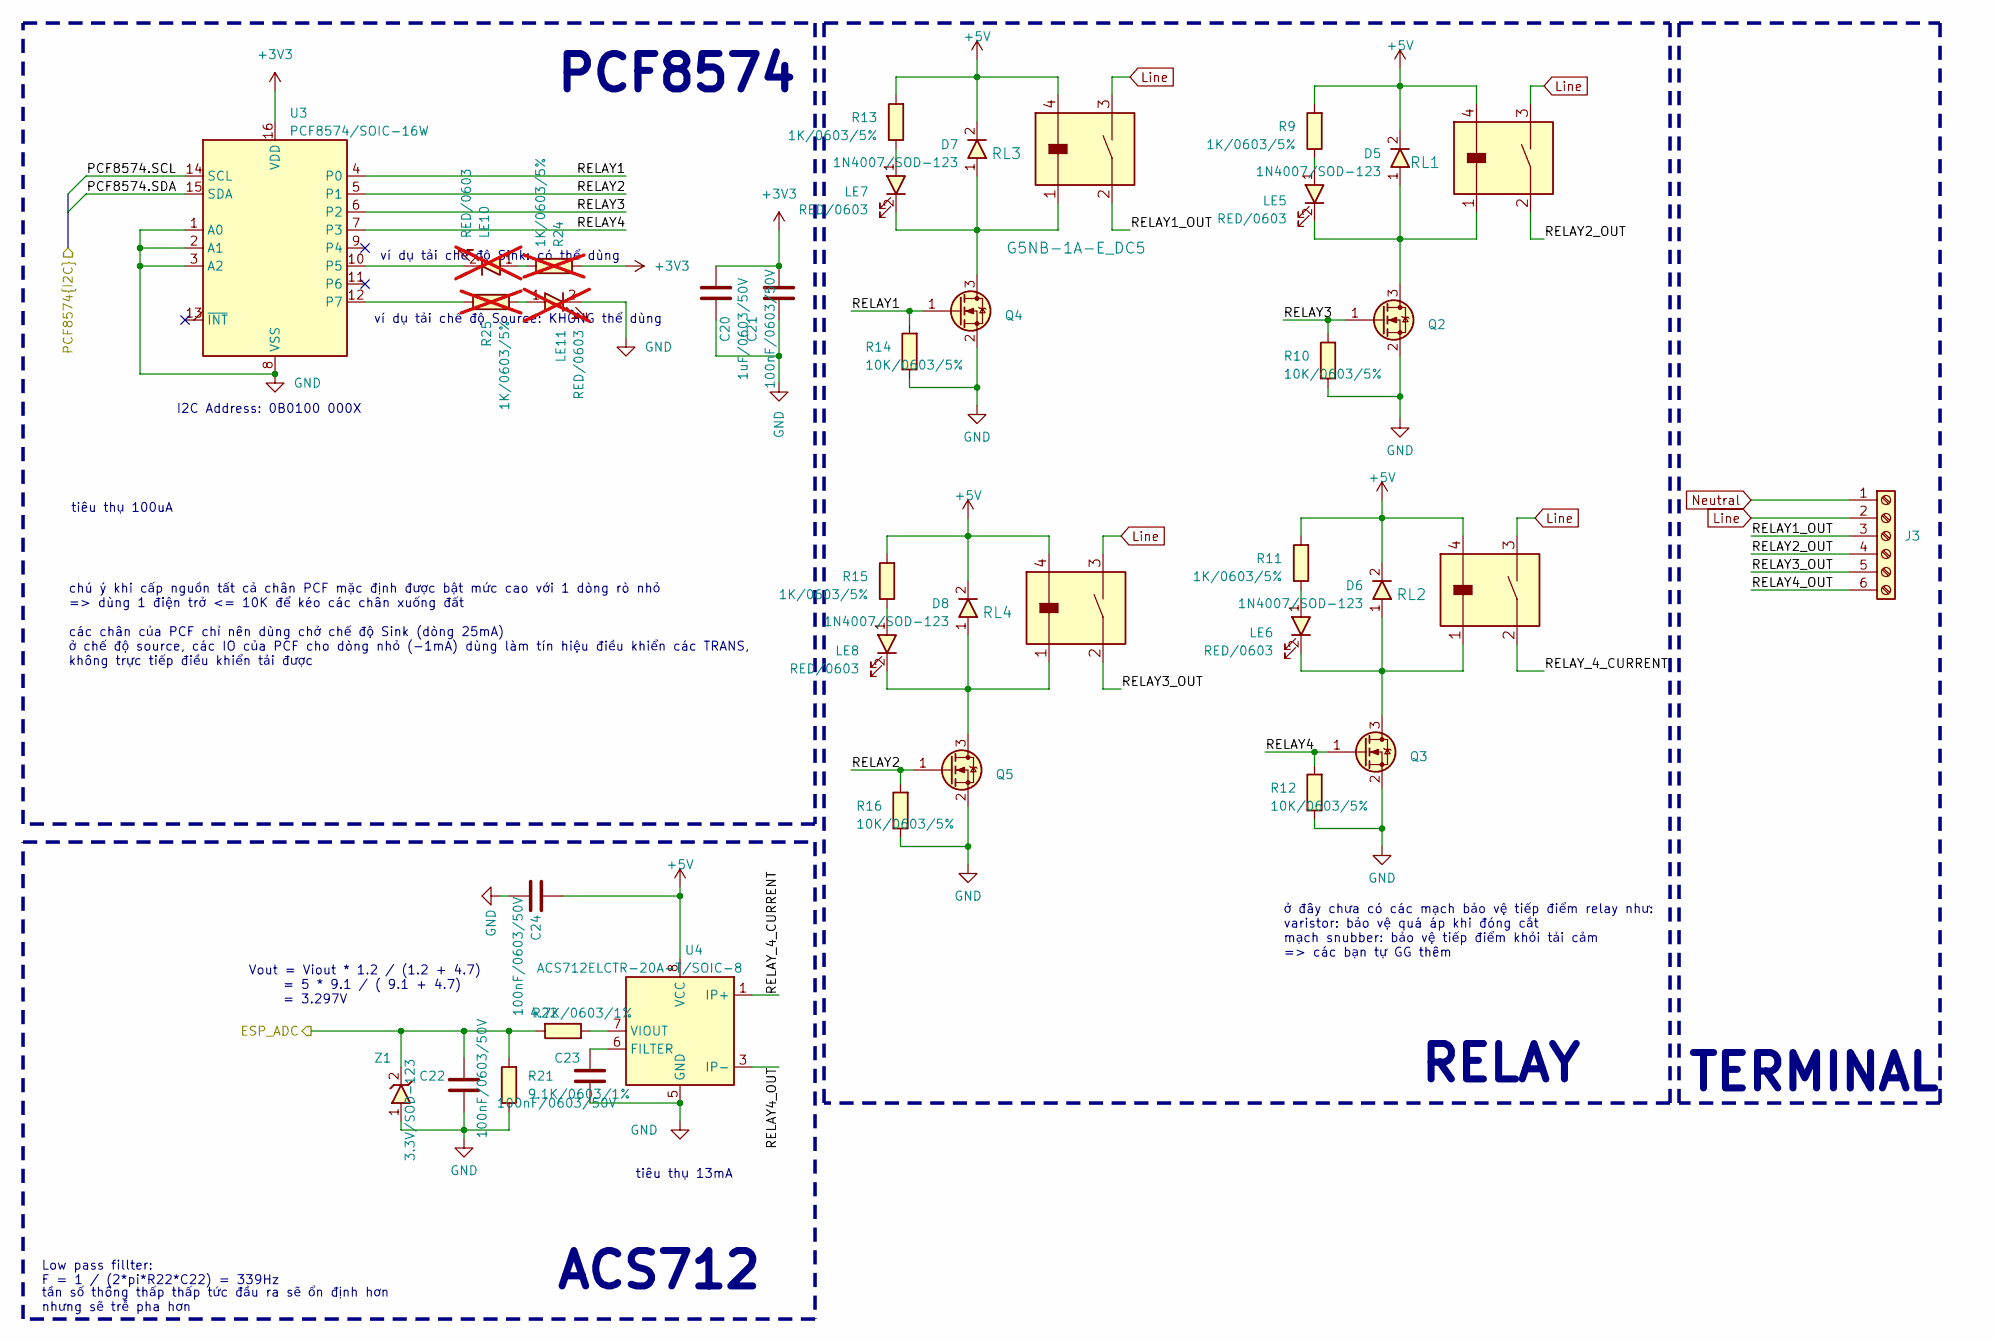
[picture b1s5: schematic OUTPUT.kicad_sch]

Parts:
C20: 1uF/0603/50V; C_0603
C21, C22, C23, C24: 100nF/0603/50V; C_0603
D5, D6, D7, D8: 1N4007/SOD-123; D_SOD-123
J3: HB9500-6P; TerminalBlock_Screw_HB9500_6P_P9.5mm
LE5, LE6, LE7, LE8: RED/0603; LED_0603
LE10, LE11: RED/0603; LED_0603; not fitted
Q2, Q3, Q4, Q5: SI2300/SOT23-3; SOT23-3
R9, R11, R13, R15: 1K/0603/5%; C_0603
R10, R12, R14, R16: 10K/0603/5%; C_0603
R21: 9.1K/0603/1%; C_0603
R22: 4.7K/0603/1%; C_0603
R24, R25: 1K/0603/5%; R_0603; not fitted
RL1, RL2, RL3, RL4: G5NB-1A-E_DC5; Relay_G5NB-1A-E DC5
U3: PCF8574/SOIC-16W; SOIC-16W_7.5x10.3mm_P1.27mm
U4: ACS712ELCTR-20A-T/SOIC-8; SOIC-8_3.9x4.9mm_P1.27mm
Z1: 3.3V/SOD-123; D_SOD-123

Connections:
+3.3V: C20.2, C21.2, R24.1, U3.16 (VDD); also elsewhere on the board
+5V: C24.1, D5.2, D6.2, D7.2, D8.2, R9.1, R11.1, R13.1, R15.1, RL1.4, RL2.4, RL3.4, RL4.4, U4.8 (VCC); also elsewhere on the board
/ESP32/ADC: C22.1, R21.1, R22.1, Z1.2; also elsewhere on the board
/RELAY/RELAY1: Q4.1 (G), R14.1, U3.4 (P0)
/RELAY/RELAY1_OUT: J3.3, RL3.2
/RELAY/RELAY2: Q5.1 (G), R16.1, U3.5 (P1)
/RELAY/RELAY2_OUT: J3.4, RL1.2
/RELAY/RELAY3: Q2.1 (G), R10.1, U3.6 (P2)
/RELAY/RELAY3_OUT: J3.5, RL4.2
/RELAY/RELAY4: Q3.1 (G), R12.1, U3.7 (P3)
/RELAY/RELAY4_OUT: J3.6, U4.3 (IP-), U4.4 (IP-)
/RELAY/RELAY_4_CURRENT: RL2.2, U4.1 (IP+), U4.2 (IP+)
GND: C20.1, C21.1, C22.2, C23.2, C24.2, LE11.2, Q2.2 (S), Q3.2 (S), Q4.2 (S), Q5.2 (S), R10.2, R12.2, R14.2, R16.2, R21.2, U3.1 (A0), U3.2 (A1), U3.3 (A2), U3.8 (VSS), U4.5 (GND), Z1.1; also elsewhere on the board
Line: J3.2, RL1.3, RL2.3, RL3.3, RL4.3; also elsewhere on the board
unnamed: LE5.1, R9.2
unnamed: LE6.1, R11.2
unnamed: LE7.1, R13.2
unnamed: LE8.1, R15.2
unnamed: LE10.1, R24.2
unnamed: LE11.1, R25.2
unnamed: D5.1, LE5.2, Q2.3 (D), RL1.1
unnamed: D6.1, LE6.2, Q3.3 (D), RL2.1
unnamed: D7.1, LE7.2, Q4.3 (D), RL3.1
unnamed: D8.1, LE8.2, Q5.3 (D), RL4.1
unnamed: LE10.2, U3.10 (P5)
unnamed: R25.1, U3.12 (P7)
unnamed: C23.1, U4.6 (FILTER)
unnamed: R22.2, U4.7 (VIOUT)
Neutral: J3.1; also elsewhere on the board

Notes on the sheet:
ở đây chưa có các mạch bảo vệ tiếp điểm relay như: varistor: bảo vệ quá áp khi đóng cắt mạch snubber: bảo vệ tiếp điểm khỏi tải cảm => các bạn tự GG thêm
TERMINAL
I2C Address: 0B0100 000X
ACS712
RELAY
ví dụ tải chế độ Source: KHÔNG thể dùng
chú ý khi cấp nguồn tất cả chân PCF mặc định được bật mức cao với 1 dòng rò nhỏ => dùng 1 điện trở <= 10K để kéo các chân xuống đất các chân của PCF chỉ nên dùng chở chế độ Sink (dòng 25mA) ở chế độ source, các IO của PCF cho dòng nhỏ (-1mA) dùng làm tín hiệu điều khiển các TRANS, không trực tiếp đ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
Low pass fillter: F = 1 / (2*pi*R22*C22) = 339Hz
tiêu thụ 100uA
PCF8574
Vout = Viout * 1.2 / (1.2 + 4.7) = 5 * 9.1 / ( 9.1 + 4.7) = 3.297V
tần số thông thấp thấp tức đầu ra sẽ ổn định hơn nhưng sẽ trễ pha hơn
ví dụ tải chế độ Sink: có thể dùng
tiêu thụ 13mA
